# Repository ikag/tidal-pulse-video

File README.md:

tidal-video-pulse
=================

An analog video synth made with Arduino that flashes drawn images to the
screen on each pulse from Tidal.

Tested with an Arduino Uno and Arduino v1.0.6

## Source code

Install [Arturo](https://github.com/scottdarch/Arturo) and compile with:

    $ ano build

To upload use:

    $ ano upload

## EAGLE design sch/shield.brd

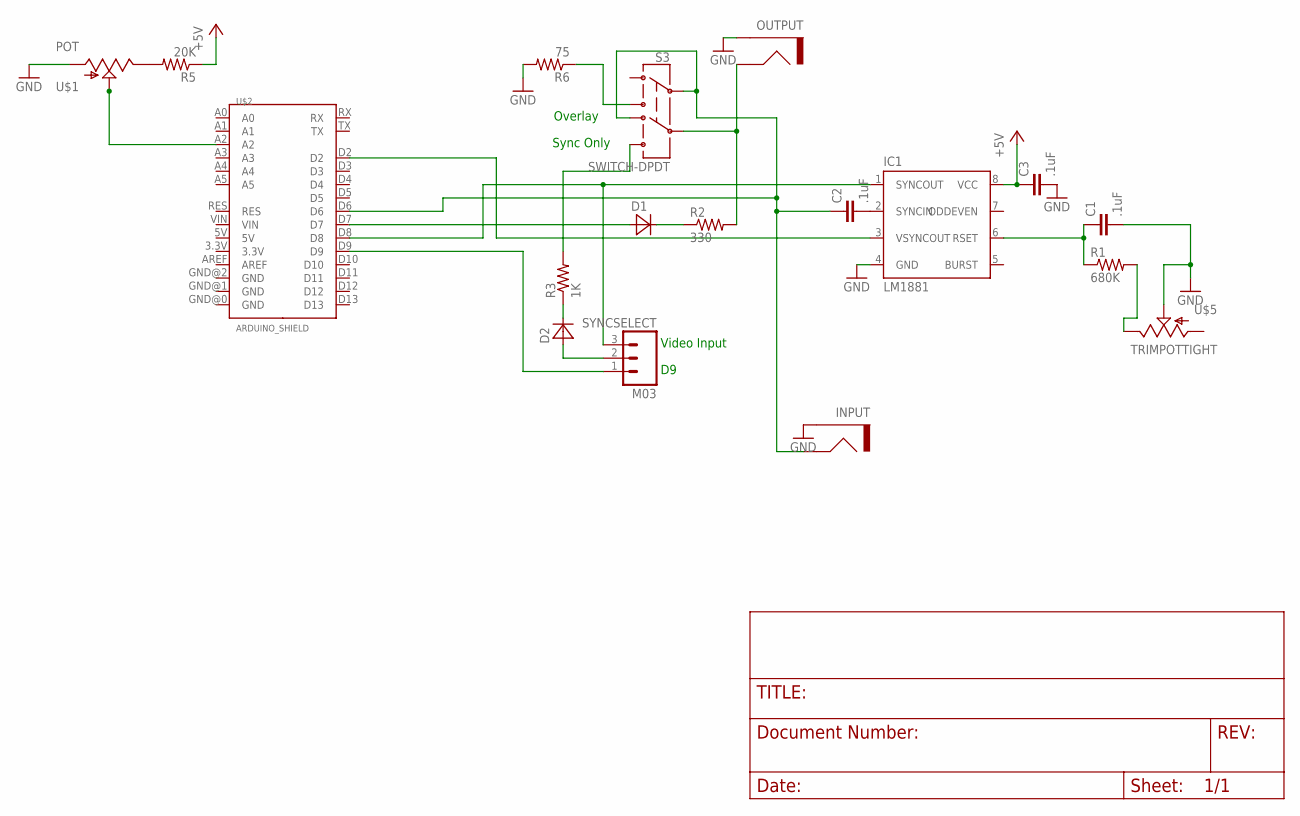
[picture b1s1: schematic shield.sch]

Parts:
C1, C2, C3: .1uF; CAP-CERAMIC-SMALL
D1, D2: 1N4148; D35-10
IC1: LM1881; DIL08
INPUT: RCAJACK; RCA
OUTPUT: RCAJACK; RCA
R1: 680K; 0207/10
R2: 330; 0207/10
R3: 1K; 0207/10
R5: 20K; 0207/10
R6: 75; 0207/10
S3: SWITCH-DPDT; OS
SYNCSELECT: M03; 1X03
U$1: POT; TRIMMERPOT
U$2: ARDUINO_SHIELD; DUEMILANOVE_SHIELD
U$5: TRIMPOTTIGHT; TRIM_POT_TIGHT

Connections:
+5V: C3.1, IC1.8 (VCC), R5.1
A2: U$1.2 (WIPER), U$1.4 (WIPER), U$2.A2
D9: SYNCSELECT.1 (2), U$2.D9
GND: C1.2, C3.2, IC1.4 (GND), INPUT.BARREL (GND), OUTPUT.BARREL (GND), R6.2, U$1.1, U$5.2
unnamed: R3.2, S3.6
unnamed: R6.1, S3.3
unnamed: D1.C, R2.1
unnamed: R1.2, U$5.3
unnamed: R5.2, U$1.3
unnamed: D2.C, R3.1
unnamed: D2.A, SYNCSELECT.2 (3)
unnamed: C2.2, IC1.2 (SYNCIN)
RSET: C1.1, IC1.6 (RSET), R1.1
SYNCOUT: IC1.1 (SYNCOUT), SYNCSELECT.3 (4), U$2.D8
VIDEOINPUT: C2.1, INPUT.P$2 (SIGNAL), S3.2, S3.4, U$2.D6
VIDEOOUT: D1.A, U$2.D7
VIDEOOUTPUT: OUTPUT.P$2 (SIGNAL), R2.2, S3.5
VSYNC: IC1.3 (VSYNCOUT), U$2.D2

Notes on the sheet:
Video Input
Overlay
Sync Only

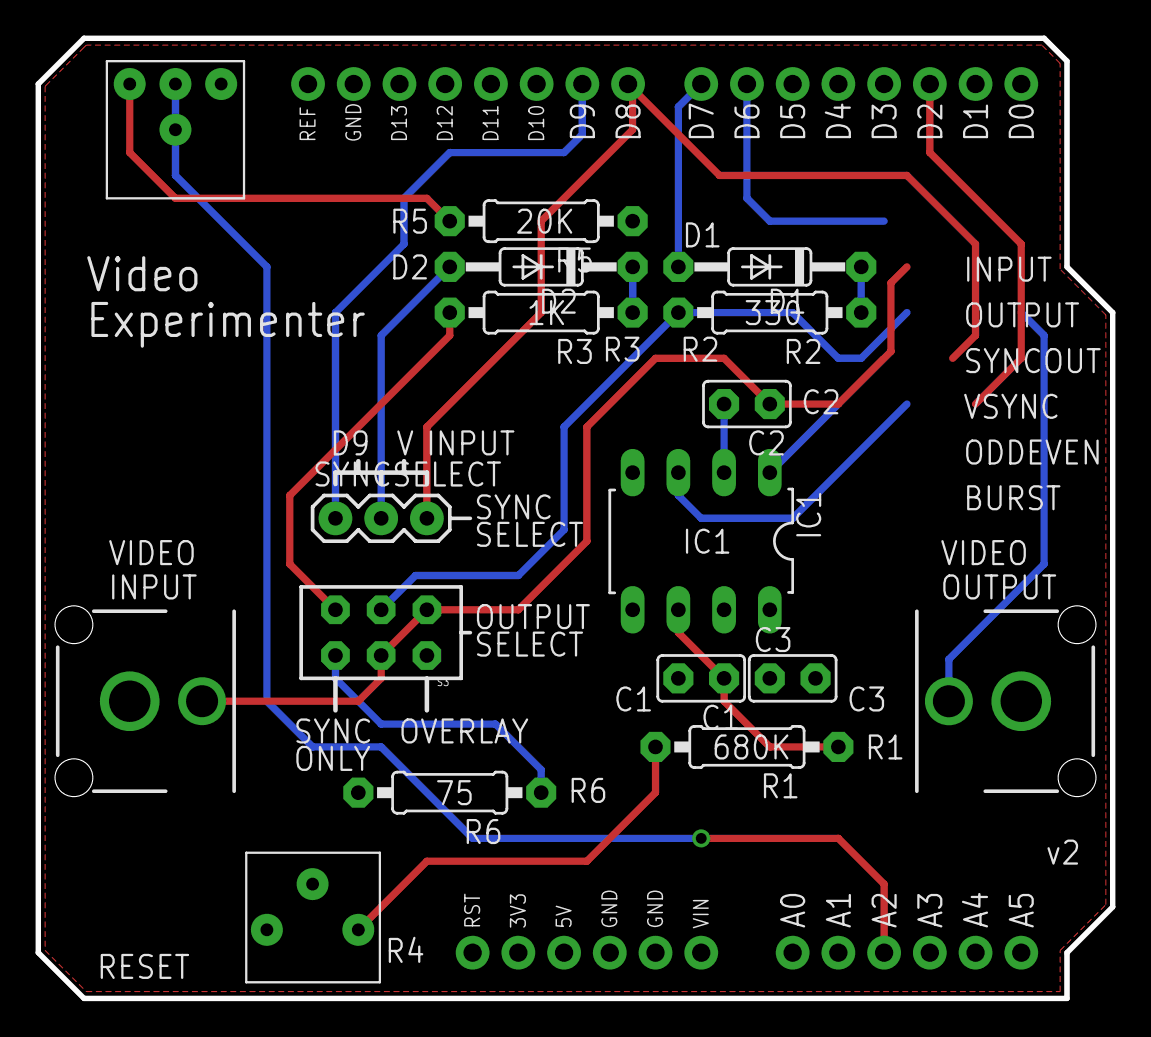
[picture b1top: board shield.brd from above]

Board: 2 copper layers, 59.7 x 53.3 mm, 18 parts (0 on the bottom side), 18 nets.

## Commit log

2016-02-03 Import Eagle board and schematics from Video Experimenter 2.0
    http://nootropicdesign.com/ve/design.html
2016-02-03 Import TVout version of nootropics for Video Experimenter
2016-02-03 Ignore temp files from Eagle
2016-02-03 sch: Remove unneeded connections
2016-02-03 Import text overlay example
2016-02-03 Draw a circle every second for 200ms
2016-02-04 Import Sync-by-serialport example from Tidal
    Change device and sent values
2016-02-04 Use pollserial for polling serial data
    Draw a circle for some ms each cycle.
2016-02-04 Update schematic pdf
2016-02-05 Draw rects on each corner for each 4/4 beat
2016-02-05 Read pot at A2 to redefine pulse_dur
2016-11-02 Ignore Ano build directory
2016-11-05 New version with more pots and buttons to control shape
2016-11-05 Read button inputs
2016-11-20 Trying new things
2017-01-17 Remove tone-related code from TVout
2017-01-17 Change pinout of buttons
2017-01-19 Various fixes
    Smooth pot readings (x, y and size)
    Triangle shape (?)
